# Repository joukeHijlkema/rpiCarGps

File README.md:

# rpiCarGps
A replacement for the speed indicator of my old van (and it does GPS and a lot more)

# Instalation

## for my screen and temp sensor
	[waveshare 7" touchscreen](http://www.waveshare.com/wiki/7inch_HDMI_LCD)

	add this to end of /boot/config.txt

	max_usb_current=1
	hdmi_group=2
	hdmi_mode=87
	hdmi_cvt 1024 600 60 6 0 0 0
	
	dtoverlay=w1-gpio
	
## for the adafruit GPS

	this is for my jessie version look at [adafruit](https://learn.adafruit.com/adafruit-ultimate-gps-on-the-raspberry-pi/using-uart-instead-of-usb) for details. (this needs to be done after gpsd instalation.
	
	-in /boot/cmdline.txt remove console=serial0,115200
	-sudo systemctl stop serial-getty@ttyS0.service
	-sudo systemctl disable serial-getty@ttyS0.service
	-add enable_uart=1 to the end of /boot/config.txt
	-add GPSD_OPTIONS="/dev/ttyS0 -F /var/run/gpsd.sock" to the end of /etc/default/gpsd
	
## SSH

	to allow for ssh acess
	touch /boot/ssh

## dependencies
	sudo apt install navit* mariadb-server gpsd gpsd-clients git gir1.2-rsvg-2.0 python-gi-cairo python3-cairo libgeos-c1v5
	sudo -H pip3 install gps3 mysql-connector==2.1.6 arrow fatskml shapely

        And if you wbat to use the extraction script

	sudo apt install libgeos-c1v5
        sudo -H pip3 install fastkml shapely geopy
	
## git repository but you probably already have it if you're reading this

``` script
git clone https://github.com/joukeHijlkema/rpiCarGps.git <gpsDir>
```

## for the database (the file lives in th DB directory)
	mysql> CREATE DATABASE busGps;
	mysql> USE busGps;
	mysql> SOURCE busGps.sql;
	mysql> CREATE USER 'Jouke'@'localhost' IDENTIFIED BY '!Jouke';
	mysql> GRANT SELECT, INSERT, UPDATE, DELETE ON `busGps`.* TO 'Jouke'@'localhost';

## the config file
To avoid trashing the config file when pulling from git there is a sample file called rpiCarGps.sample in the root directory.
copy this file to <gpsDir>/rpiCarGps.cfg

## switch off screen blanking
	change two settings in /etc/kbd/config 
	BLANK_TIME=0
	POWERDOWN_TIME=0

	add the folowing lines to /etc/xdg/lxsession/LXDE/autostart and /etc/xdg/lxsession/LXDE-pi/autostart
	#@xscreensaver -no-splash
	@xset s off
	@xset -dpms
	@xset s noblank

## Maps
- Copy all your maps to /home/pi/Maps/
- Copy or link <gpsDir>/GPS/myNavit.xml to ~/.navit/navit.xml

## to auto start
put a file called rpiGps.desktop in ~/.config/autostart containing :

``` script
[Desktop Entry]
Type=Application
Exec=/home/pi/Projects/rpiCarGps/run.py
Hidden=false
X-GNOME-Autostart-enabled=true
Name=rpiCarGps
Comment=rpiCarGps
Terminal=false
Icon=/home/pi/Projects/rpiCarGps/GUI/Icons/compass.png
Path=/home/pi/Projects/rpiCarGps/
StartupNotify=false
```

## Python
I switched to glade for the GUI. The catalog file is in GLADE/CATALOG

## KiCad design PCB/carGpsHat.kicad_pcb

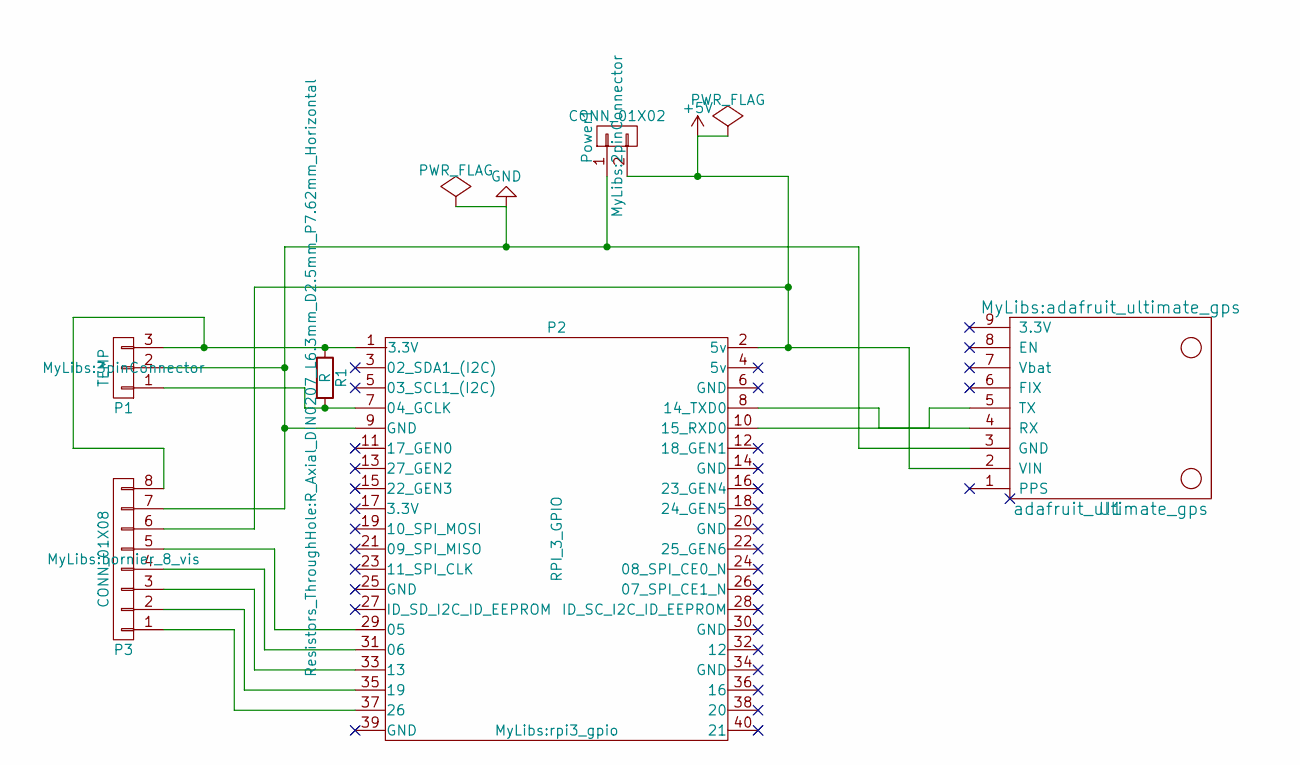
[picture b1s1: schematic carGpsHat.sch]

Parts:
P1: TEMP; 3pinConnector
P2: RPI_3_GPIO; rpi3_gpio
P3: CONN_01X08; bornier_8_vis
Power1: CONN_01X02; 2pinConnector
R1: R; R_Axial_DIN0207_L6.3mm_D2.5mm_P7.62mm_Horizontal
U1: adafruit_ultimate_gps

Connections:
+5V: P2.2 (5v), P3.6, Power1.2, U1.2 (VIN)
GND: P1.2, P2.9 (GND), P3.7, Power1.1, U1.3 (GND)
unnamed: P1.1, P2.7 (04_GCLK), R1.2
unnamed: P1.3, P2.1 (3.3V), P3.8, R1.1
unnamed: P2.8 (14_TXD0), U1.4 (RX)
unnamed: P2.10 (15_RXD0), U1.5 (TX)
unnamed: P2.29 (05), P3.5
unnamed: P2.31 (06), P3.4
unnamed: P2.33 (13), P3.3
unnamed: P2.35 (19), P3.2
unnamed: P2.37 (26), P3.1

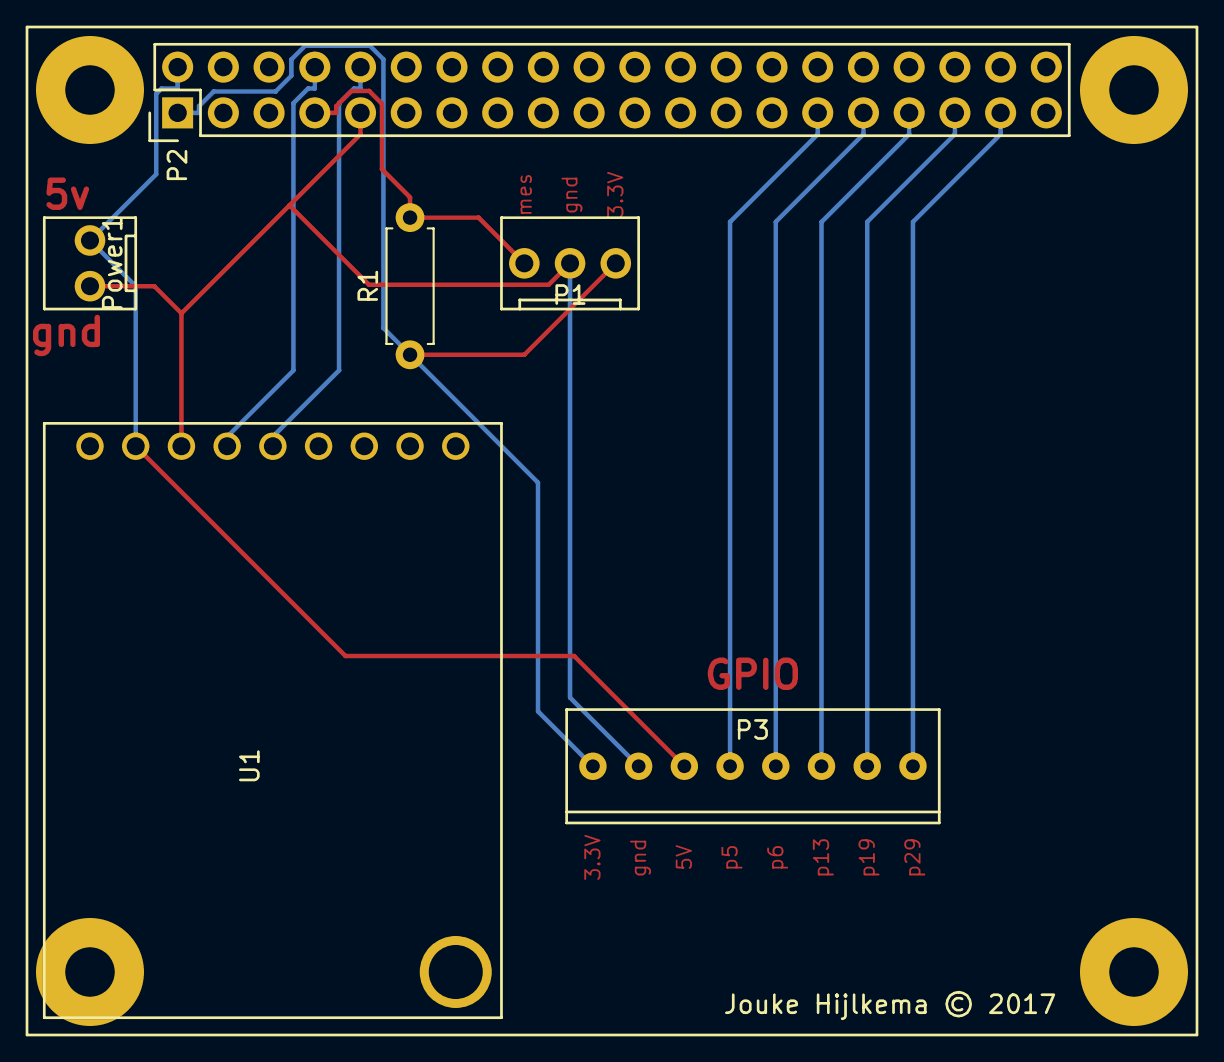
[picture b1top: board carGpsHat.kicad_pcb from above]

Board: 2 copper layers, 6 parts (0 on the bottom side), 11 nets.

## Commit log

2017-02-17 import existing stuff
2017-02-18 3D Box drawwings
2017-03-05 drwwing box finished
2017-03-05 pcb and ordered finished
2017-03-05 temp measurement working
2017-04-04 new box
2017-04-20 gtk gui version works better than QT I feel
2017-04-21 working GTK version
2017-04-21 befor pull
2017-05-05 first working version. did 160 km
2017-07-15 catastrophy reinstall
2017-07-15 detect if running on rpi or not
2017-07-15 bug fix in temp
2017-07-15 bug fix in gui
2017-07-16 fix bug in root path detection
2017-07-16 back button for day distance (couldn't get spin button to work)
2017-07-16 added label change for dayDist
2017-07-16 added trip reset and optimised total distance calculation
2017-07-16 bug fix db
2017-07-16 bug fix in db
2017-07-16 more bug fixes
2017-08-17 return holiday trip 2017, works fine
2017-08-17 added Data dir to be ignored
2017-08-30 version with glade
2017-08-30 config file
2017-08-30 bug fixes
2017-08-30 gps to use gps3
2017-08-30 different layouts
2017-08-30 trying to fix css bug. Not working, trying to install python 3.6.2
2017-08-30 debugging css
2017-08-31 box for Vero
2017-09-12 box vero
2018-10-28 back from trip to genova
2018-10-28 new version
2019-08-15 radio element
2019-12-01 gps frame
2020-02-29 radio wip
2020-08-28 new boxer install
2020-08-29 first level implementation
2020-08-29 Boxer drawings
2020-08-29 New GUI with Level
2020-09-25 back from trip 2020
2021-03-13 Addded MPD tab. It almost works
2021-08-15 before 2021 vacations
2021-09-22 retour norway
2022-08-14 removed navit source. Use package
2022-08-15 bug fixes 2022. Good spot button.
2022-09-17 back from Montenegro
2022-09-17 after Montenegro

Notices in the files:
parts and their libraries:
Jouke Hijlkema © 2017
